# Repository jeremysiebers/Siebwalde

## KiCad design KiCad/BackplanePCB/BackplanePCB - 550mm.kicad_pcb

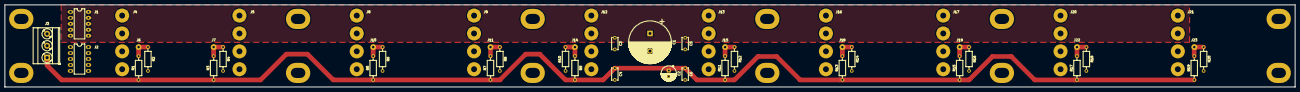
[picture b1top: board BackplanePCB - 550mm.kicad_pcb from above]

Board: 2 copper layers, 550.0 x 35.0 mm, 61 parts (0 on the bottom side), 13 nets.

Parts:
C1: 4700u; CP_Radial_D18.0mm_P7.50mm
C2: 100u; CP_Radial_D6.3mm_P2.50mm
C3, C4: 100n; C_Disc_D5.0mm_W2.5mm_P5.00mm
C5, C6: 2.2u; C_Disc_D5.0mm_W2.5mm_P5.00mm
J1, J2: Powerbug DIP10; DIP-10_W7.62mm_LongPads
J3: Conn_01x03; TerminalBlock_Phoenix_MKDS-3-3-5.08_1x03_P5.08mm_Horizontal
J4, J5, J8, J9, J12, J13, J16, J17, J20, J21: Conn_01x04; SolderWirePad_4xinLine_2-5mmDrill
J6, J7, J10, J11, J14, J15, J18, J19, J22, J23: Conn_01x01; SolderWirePad_single_1mmDrill
MK1, MK2, MK3, MK4, MK5, MK6, MK7, MK8, MK9, MK10, MK11, MK12: Mounting_Hole_PAD; MountingHole_4.3x6.2mm_M4_Pad
R1, R3, R5, R7, R9, R11, R13, R15, R17, R19: 909E; R_Axial_DIN0207_L6.3mm_D2.5mm_P10.16mm_Horizontal
R2, R4, R6, R8, R10, R12, R14, R16, R18, R20: 9k53; R_Axial_DIN0207_L6.3mm_D2.5mm_P10.16mm_Horizontal

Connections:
+5V: C2.1, C4.1, C6.1, J3.1, R1.1, R3.1, R5.1, R7.1, R9.1, R11.1, R13.1, R15.1, R17.1, R19.1
+15V: C1.1, C3.1, C5.1, J1.1, J1.2, J1.3, J1.4, J1.5, J1.6, J1.7, J1.8, J1.9, J1.10, J4.1, J4.2, J5.1, J5.2, J8.1, J8.2, J9.1, J9.2, J12.1, J12.2, J13.1, J13.2, J16.1, J16.2, J17.1, J17.2, J20.1, J20.2, J21.1, J21.2
GND: C1.2, C2.2, C3.2, C4.2, C5.2, C6.2, J2.1, J2.2, J2.3, J2.4, J2.5, J2.6, J2.7, J2.8, J2.9, J2.10, J3.3, J4.3, J4.4, J5.3, J5.4, J8.3, J8.4, J9.3, J9.4, J12.3, J12.4, J13.3, J13.4, J16.3, J16.4, J17.3, J17.4, J20.3, J20.4, J21.3, J21.4, MK1.1, MK2.1, MK3.1, MK4.1, MK5.1, MK6.1, MK7.1, MK8.1, MK9.1, MK10.1, MK11.1, MK12.1, R2.2, R4.2, R6.2, R8.2, R10.2, R12.2, R14.2, R16.2, R18.2, R20.2
unnamed: J6.1, R1.2, R2.1
unnamed: J7.1, R3.2, R4.1
unnamed: J10.1, R5.2, R6.1
unnamed: J11.1, R7.2, R8.1
unnamed: J14.1, R9.2, R10.1
unnamed: J15.1, R11.2, R12.1
unnamed: J18.1, R13.2, R14.1
unnamed: J19.1, R15.2, R16.1
unnamed: J22.1, R17.2, R18.1
unnamed: J23.1, R19.2, R20.1

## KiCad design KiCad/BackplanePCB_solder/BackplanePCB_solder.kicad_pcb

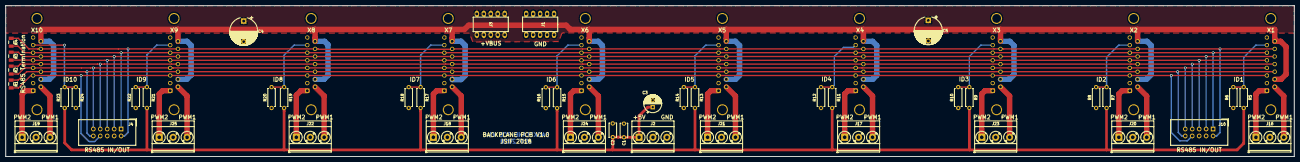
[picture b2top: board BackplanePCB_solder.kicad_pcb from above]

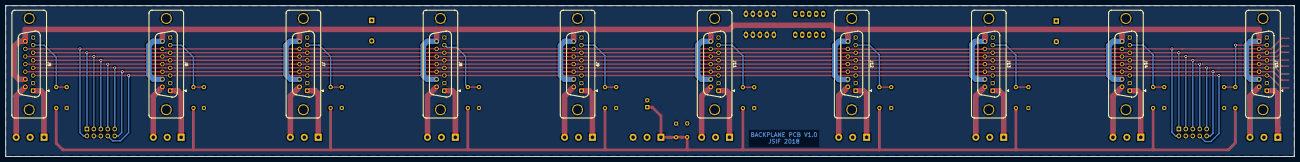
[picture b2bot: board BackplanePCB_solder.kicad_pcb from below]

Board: 2 copper layers, 470.0 x 55.0 mm, 54 parts (10 on the bottom side), 41 nets.

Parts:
C1: 100n; C_Disc_D5.0mm_W2.5mm_P5.00mm
C2: 22u; C_Disc_D5.0mm_W2.5mm_P5.00mm
C3: 100u; CP_Radial_D6.3mm_P2.50mm
C4, C5: 470u; CP_Radial_D10.0mm_P7.50mm
J1: PowerBug_GND; DIP-10_W7.62mm
J2, J16, J17, J18, J19, J20, J21, J22, J23, J24, J25: Conn_01x03; TerminalBlock_Phoenix_MKDS-3-3-5.08_1x03_P5.08mm_Horizontal
J3: PowerBug+17V; DIP-10_W7.62mm
J4, J10: Conn_02x05_Odd_Even; IDC-Header_2x05_P2.54mm_Vertical
J5, J6, J7, J8, J9, J11, J12, J13, J14, J15: DB15_Female_MountingHoles; DSUB-15_Female_Vertical_P2.77x2.84mm_MountingHoles
R1, R2, R3, R4: 120E; R_1206_3216Metric
R5, R6, R7, R8, R9, R10, R11, R12, R13, R14, R15, R16, R17, R18, R19, R20, R21, R22, R23, R24: R; R_Axial_DIN0207_L6.3mm_D2.5mm_P7.62mm_Horizontal

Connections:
+5V: C1.1, C2.1, C3.1, J2.1, R5.2, R7.2, R9.2, R11.2, R13.2, R15.2, R17.2, R19.2, R21.2, R23.2
+15V: C4.1, C5.1, J3.1, J3.2, J3.3, J3.4, J3.5, J3.6, J3.7, J3.8, J3.9, J3.10, J5.10, J5.15, J6.10, J6.15, J7.10, J7.15, J8.10, J8.15, J9.10, J9.15, J11.10, J11.15, J12.10, J12.15, J13.10, J13.15, J14.10, J14.15, J15.10, J15.15
/ID_1: J5.7, R5.1, R6.2
/ID_2: J6.7, R7.1, R8.2
/ID_3: J7.7, R9.1, R10.2
/ID_4: J8.7, R11.1, R12.2
/ID_5: J9.7, R13.1, R14.2
/ID_6: J11.7, R15.1, R16.2
/ID_7: J12.7, R17.1, R18.2
/ID_8: J13.7, R19.1, R20.2
/ID_9: J14.7, R21.1, R22.2
/ID_10: J15.7, R23.1, R24.2
/PWMO1_1: J5.9, J16.3
/PWMO1_2: J6.9, J20.3
/PWMO1_3: J7.9, J23.3
/PWMO1_4: J8.9, J17.3
/PWMO1_5: J9.9, J21.3
/PWMO1_6: J11.9, J24.3
/PWMO1_7: J12.9, J18.3
/PWMO1_8: J13.9, J22.3
/PWMO1_9: J14.9, J25.3
/PWMO1_10: J15.9, J19.3
/PWMO2_1: J5.1, J16.1
/PWMO2_2: J6.1, J20.1
/PWMO2_3: J7.1, J23.1
/PWMO2_4: J8.1, J17.1
/PWMO2_5: J9.1, J21.1
/PWMO2_6: J11.1, J24.1
/PWMO2_7: J12.1, J18.1
/PWMO2_8: J13.1, J22.1
/PWMO2_9: J14.1, J25.1
/PWMO2_10: J15.1, J19.1
/RESET_A: J4.2, J5.14, J6.14, J7.14, J8.14, J9.14, J10.2, J11.14, J12.14, J13.14, J14.14, J15.14, R4.2
/RESET_B: J4.1, J5.6, J6.6, J7.6, J8.6, J9.6, J10.1, J11.6, J12.6, J13.6, J14.6, J15.6, R4.1
/RX_A: J4.10, J5.11, J6.11, J7.11, J8.11, J9.11, J10.10, J11.11, J12.11, J13.11, J14.11, J15.11, R1.2
/RX_B: J4.8, J5.3, J6.3, J7.3, J8.3, J9.3, J10.8, J11.3, J12.3, J13.3, J14.3, J15.3, R1.1
/SYNC_A: J4.3, J5.13, J6.13, J7.13, J8.13, J9.13, J10.3, J11.13, J12.13, J13.13, J14.13, J15.13, R3.2
/SYNC_B: J4.5, J5.5, J6.5, J7.5, J8.5, J9.5, J10.5, J11.5, J12.5, J13.5, J14.5, J15.5, R3.1
/TX_A: J4.7, J5.12, J6.12, J7.12, J8.12, J9.12, J10.7, J11.12, J12.12, J13.12, J14.12, J15.12, R2.2
/TX_B: J4.9, J5.4, J6.4, J7.4, J8.4, J9.4, J10.9, J11.4, J12.4, J13.4, J14.4, J15.4, R2.1
GND: C1.2, C2.2, C3.2, C4.2, C5.2, J1.1, J1.2, J1.3, J1.4, J1.5, J1.6, J1.7, J1.8, J1.9, J1.10, J2.3, J4.4, J4.6, J5.0, J5.2, J5.8, J6.0, J6.2, J6.8, J7.0, J7.2, J7.8, J8.0, J8.2, J8.8, J9.0, J9.2, J9.8, J10.4, J10.6, J11.0, J11.2, J11.8, J12.0, J12.2, J12.8, J13.0, J13.2, J13.8, J14.0, J14.2, J14.8, J15.0, J15.2, J15.8, R6.1, R8.1, R10.1, R12.1, R14.1, R16.1, R18.1, R20.1, R22.1, R24.1

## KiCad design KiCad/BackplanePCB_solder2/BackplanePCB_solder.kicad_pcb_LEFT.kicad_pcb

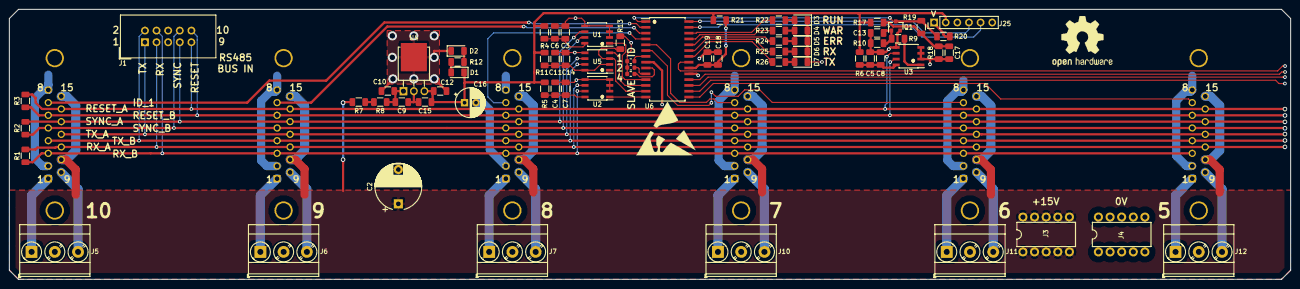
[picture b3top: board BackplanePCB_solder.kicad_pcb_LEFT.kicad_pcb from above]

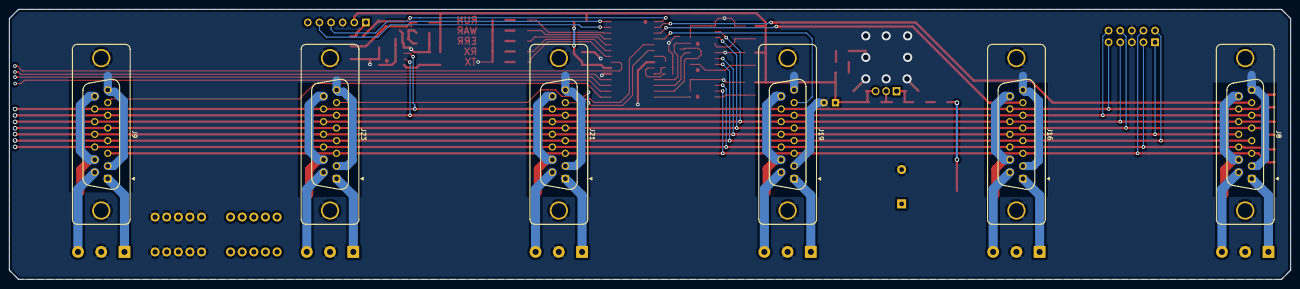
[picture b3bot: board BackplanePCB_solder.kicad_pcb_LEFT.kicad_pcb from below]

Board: 2 copper layers, 280.0 x 59.0 mm, 74 parts (6 on the bottom side), 62 nets.

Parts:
C2: 470u; CP_Radial_D10.0mm_P7.50mm
C3, C4, C5, C6, C7, C8, C9, C10, C11, C12, C13, C14, C15, C17, C18, C19: C; C_1206_3216Metric
C16: CP; CP_Radial_D6.3mm_P2.50mm
D1: D_Zener; D_1206_3216Metric
D2: LED; D_1206_3216Metric
D3, D6, D7: LED GR; D_1206_3216Metric
D4: LED YE; D_1206_3216Metric
D5: LED RD; D_1206_3216Metric
J1: Conn_02x05_Odd_Even; IDC-Header_2x05_P2.54mm_Vertical
J3: PowerBug+15V; DIP-10_W7.62mm
J4: PowerBug_GND; DIP-10_W7.62mm
J5, J6, J7, J10, J11, J12: Conn_01x03; TerminalBlock_Phoenix_MKDS-3-3-5.08_1x03_P5.08mm_Horizontal
J8, J9, J16, J19, J21, J23: DB15_Female_MountingHoles; DSUB-15_Female_Vertical_P2.77x2.84mm_MountingHoles
J25: Conn_01x06; PinHeader_1x06_P2.54mm_Vertical
Q1: Q_NMOS_GSD; SOT-23
R1, R2, R3: 120E; R_1206_3216Metric
R4, R5, R6, R7, R8, R9, R10, R11, R12, R13, R17, R18, R19, R20, R21, R22, R23, R24, R25, R26: R; R_1206_3216Metric
R14, R15, R16: R; R_0603_1608Metric
U1, U2, U3, U5: ST485EBDR; SOIC-8_3.9x4.9mm_P1.27mm
U4: KA78M05_TO252; TO-251-3-1EP_Horizontal_TabDown
U6: PIC16F18854-SO; SOIC-28W_7.5x17.9mm_P1.27mm

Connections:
+5V: C12.1, C15.1, C16.1, D1.1, J25.2, R4.2, R5.2, R6.2, R11.2, R17.2, R21.1, U4.3
+15V: C2.1, J3.1, J3.2, J3.3, J3.4, J3.5, J3.6, J3.7, J3.8, J3.9, J3.10, J8.10, J8.15, J9.10, J9.15, J16.10, J16.15, J19.10, J19.15, J21.10, J21.15, J23.10, J23.15, R7.2
/PWMO1_1: J5.3, J8.9
/PWMO1_2: J6.3, J16.9
/PWMO1_3: J7.3, J19.9
/PWMO1_4: J10.3, J21.9
/PWMO1_5: J11.3, J23.9
/PWMO1_6: J9.9, J12.3
/PWMO2_1: J5.1, J8.1
/PWMO2_2: J6.1, J16.1
/PWMO2_3: J7.1, J19.1
/PWMO2_4: J10.1, J21.1
/PWMO2_5: J11.1, J23.1
/PWMO2_6: J9.1, J12.1
GND: C2.2, C3.2, C4.2, C5.2, C6.2, C7.2, C8.2, C9.2, C10.2, C11.2, C12.2, C13.2, C14.2, C15.2, C16.2, C17.2, C18.2, C19.2, D2.1, D3.1, D4.1, D5.1, D6.1, D7.1, J1.5, J1.6, J4.1, J4.2, J4.3, J4.4, J4.5, J4.6, J4.7, J4.8, J4.9, J4.10, J5.2, J6.2, J7.2, J8.0, J8.2, J8.8, J9.0, J9.2, J9.8, J10.2, J11.2, J12.2, J16.0, J16.2, J16.8, J19.0, J19.2, J19.8, J21.0, J21.2, J21.8, J23.0, J23.2, J23.8, J25.3, Q1.2, R10.2, R13.1, R14.2, R15.2, R16.2, R18.1, U1.2, U1.3, U1.4, U1.5, U2.2, U2.3, U2.4, U2.5, U3.2, U3.3, U3.4, U3.5, U4.2, U4.4, U5.5, U6.8, U6.19
ICSPCLK: J25.5, U6.27
ICSPDAT: J25.4, U6.28
ID_1: J8.7, U6.2
ID_2: J16.7, U6.3
ID_3: J19.7, U6.4
ID_4: J21.7, U6.5
ID_5: J23.7, U6.6
ID_6: J9.7, U6.15
unnamed: C3.1, C6.1, R4.1, U1.8
unnamed: C4.1, C7.1, R5.1, U2.8
unnamed: C5.1, C8.1, R6.1, U3.8
unnamed: C9.1, C10.1, R8.1, U4.1
unnamed: C11.1, C14.1, R11.1, U5.2, U5.8
unnamed: C13.1, Q1.1, R9.2, R10.1
unnamed: C17.1, R17.1, R18.2, R19.2
unnamed: C18.1, C19.1, R21.2, U6.20
unnamed: D1.2, R12.1
unnamed: D2.2, R12.2
unnamed: D3.2, R22.2
unnamed: D4.2, R23.2
unnamed: D5.2, R24.2
unnamed: D6.2, R25.2
unnamed: D7.2, R26.2
unnamed: R7.1, R8.2
unnamed: R9.1, U3.1
unnamed: R14.1, U6.7
unnamed: R15.1, U6.10
unnamed: R16.1, U6.9
unnamed: R22.1, U6.26
unnamed: R23.1, U6.25
unnamed: R24.1, U6.24
unnamed: R25.1, U6.23
unnamed: R26.1, U6.22
RESET_A: J1.9, J8.14, J9.14, J16.14, J19.14, J21.14, J23.14, R3.2, U3.6
RESET_B: J1.10, J8.6, J9.6, J16.6, J19.6, J21.6, J23.6, R3.1, U3.7
RST: Q1.3, R19.1, R20.2, U6.1
RX: U2.1, U6.14
RX_A: J1.3, J8.11, J9.11, J16.11, J19.11, J21.11, J23.11, R1.2, U2.6
RX_B: J1.4, J8.3, J9.3, J16.3, J19.3, J21.3, J23.3, R1.1, U2.7
SYNC: U1.1, U6.11
SYNC_A: J1.7, J8.13, J9.13, J16.13, J19.13, J21.13, J23.13, R2.2, U1.6
SYNC_B: J1.8, J8.5, J9.5, J16.5, J19.5, J21.5, J23.5, R2.1, U1.7
TX: U5.4, U6.12
TX_A: J1.1, J8.12, J9.12, J16.12, J19.12, J21.12, J23.12, U5.6
TX_B: J1.2, J8.4, J9.4, J16.4, J19.4, J21.4, J23.4, U5.7
TX_ENA: R13.2, U5.3, U6.13
VPP: J25.1, R20.1

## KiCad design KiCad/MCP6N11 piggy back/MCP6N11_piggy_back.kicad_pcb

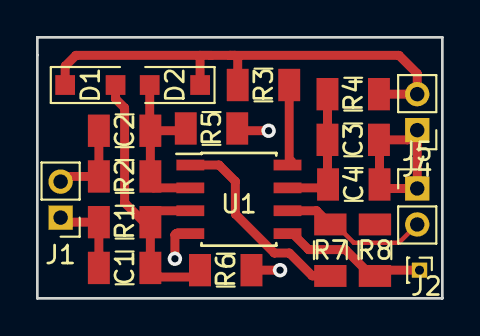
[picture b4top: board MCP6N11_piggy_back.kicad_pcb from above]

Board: 2 copper layers, 22.5 x 14.5 mm, 19 parts (0 on the bottom side), 11 nets.

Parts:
C1, C2: 22p; C_1206_3216Metric
C3: 100n; C_1206_3216Metric
C4: 2.2u; C_1206_3216Metric
D1, D2: 1n4148; D_SOD-123F
J1, J4, J5: Conn_01x02_Male; PinHeader_1x02_P2.00mm_Vertical
J2: Conn_01x01_Male; PinHeader_1x01_P1.00mm_Vertical
R1, R2: 9k10; R_1206_3216Metric
R3: 4k75; R_1206_3216Metric
R4: 10E; R_1206_3216Metric
R5, R6, R7: 1k; R_1206_3216Metric
R8: 100k; R_1206_3216Metric
U1: MCP6N11; SOIC-8_3.9x4.9mm_P1.27mm

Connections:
+5V: D1.1, D2.1, J4.2, R3.2, R4.2
GND: C3.2, C4.2, J4.1, J5.1, R5.1, R6.1, U1.4
unnamed: C1.1, D1.2, R1.1, R6.2, U1.3
unnamed: C1.2, J1.1, R1.2
unnamed: C2.1, D2.2, R2.1, R5.2, U1.2
unnamed: C2.2, J1.2, R2.2
unnamed: C3.1, C4.1, R4.1, U1.7
unnamed: J2.1, R8.1, U1.5
unnamed: J5.2, R7.2, U1.6
unnamed: R3.1, U1.8
unnamed: R7.1, R8.2, U1.1
